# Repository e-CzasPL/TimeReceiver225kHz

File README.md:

# TimeReceiver225kHz
<html>
<body>
<H1>A simple receiver module for decoding a time frame from a 225kHz transmitter PCSK-225 in Solec Kujawski, Poland</h1>

<H2>Content</H2>
<h3>English</h3>
<ul>
  <li><a href="#en1">Changes</li>
  <li><a href="#en1">What's e-Czas</a></li>
  <li><a href="#en2">What's e-Czas Radio?</a></li>
  <li><a href="#en1">Flash programming guide</a></li>
</ul>
<h3>Polski</h3>
<ul>
<li><a href="#pl0">Zmiany</a></li>
<li><a href="#pl1">Co to jest e-Czas?</a></li>
<li><a href="#pl2">Co to jest e-Czas Radio?</a></li>  
<li><a href="#pl3">Instrukcja programowania procesora</a></li>
</ul>
<h2 id="en0">Changes</h2>
<ul>
  <li><b>2024-06-11:</b> Thanks to Damian Jabłoński, who found an error in the scheme. This caused the processor to operate unstablely. Resistor R2 20k (shown in the current schematic) should be added to fix the error.</li>
   <li><b>2024-06-12:</b> 
   The repository contains corrected versions of the project files in KiCAD. In the KiCAD/1.0/bom folder, you can find the interactive BOM in HTML. In the KiCAD/1.0/production folder, you can find production (Gerber) files for fixed PCB.
   </li>
      <li><b>2024-06-14:</b> The repository contains corrected versions firmware. It doesn't need the resistor R2 (20k). Currently is used internal pull-up resistor.
   </li>

</ul>

<h2 id="en1">What's e-Czas</h2>

<p>Providing the service of reliable and reliable distribution of official time signals valid in the territory of the Republic of Poland and signals of the Polish implementation of the international coordinated universal time UTC (PL), based on the state standard for time measurement units and frequency, with the status (guarantee) of official time and synchronization monitoring service.

<h2 id="en2">What's e-Czas Radio?</h2>

<p>The e-Czas Radio service is used to distribute coded official time signals in the territory of the Republic of Poland using long radio waves. End-user synchronization accuracy: &lt;0.01 s

<p>As part of the e-CzasPL project, a service was launched for emitting coded digital time signals on long waves, using the 225 kHz carrier wave of the First Polish Radio Program, from a transmitter located in Poland (a technique similar to the DCF77 (Germany), WWVB (USA), JJY (Japan) system, but based on signal phase modulation), which creates a generally available option to synchronize any time-measuring device with the official time in the Republic of Poland using cheap, energy-saving and simple receiving devices. This technique allows many time-measuring devices to be synchronized to the official time in the Republic of Poland with an accuracy of several or a dozen milliseconds. The system is an additional (redundant) source of time information for users located in Poland.
<p>The standard signals are generated using a stable frequency module based on highly stable rubidium frequency standards in the Radio Broadcasting Center (RCN) in Solec Kujawski. Using receiving devices located at the headquarters of the Central Office of Measures in Warsaw, employees of the Time and Frequency Laboratory remotely monitor changes in the frequency of the carrier wave, as well as monitor the accuracy of encoded time signals and compare them with the Official Time Scale in force in the Republic of Poland generated and maintained in the Central Office of Measures.

<p>The technique using digitally coded time signals involves emitted radio waves from RCN Solec Kujawski and the use of dedicated receivers by end users. You can download documentation related to the technical parameters of the transmitted time signal and a description of the process of making a simplified receiver of coded official time signals on the 225 kHz carrier wave of the First Polish Radio Program.
<br><br>
<ul>
<li>In the "/doc" folder, you will find documentation (in Polish) describing how to encode and receive a time frame. 
<li>In the "/Eagle" folder, you can find the design of the receiver in Autodesk Eagle format. 
<li>In the "/KiCAD" folder, you can find the design of the receiver in KiCAD format. 
<li>In the "/Firmware" folder, you can find firmware for the DSPIC33FJ128GP804 processor in HEX format. 

</ul>

<h3>Power</h3>
<p>The best solution is to use a 5V power supply, e.g. USB. Current consumption is approximately 100mA @ 5V.</p>

<h2 id="en3">Flash programming guide</h2>
<p>I use <a href="https://www.microchip.com/en-us/development-tool/PG164150" target=_blank>PICKIT5, which is not much more expensive than the previous ones and can program without a computer, in the "field." The instructions below describe installing the required software in a Windows 11 environment.
<ol>p
<li>Install <a href="https://www.microchip.com/en-us/tools-resources/develop/mplab-x-ide" target=_blank>MPLAB X IDE</a>
<li>When you install MPLAB and connect PICKIT5 to USB, sometimes the system doesn't recognize it properly. Then open "Device Manager" and check the "Ports (COM & LPT) section. It should look like this:<br><br>
In the "Universal Serial Bus devices"<br><br>If no drivers are installed, this will show<br>>
<br>In the "Microchip Tools"<br>
<br>If the last section does not exist, you must update the drivers on your device, which will appear in the "Universal Serial Bus devices" section.
<li>Without the correct driver, the system will show the error "Failed to get Device ID. Please ensure the target device is attached and try the operation again."
<li>Check the 3V3 power supply at the output of the LM1117 stabilizer
<li>Connect the PICKIT5 programmer to the connector on the board. (pins 1 to 5)
<li>Run MPLAB IPE - specify the path to the HEX file, processor type<br>
<li>Click "Connect", the board must be powered<br>
<li>Program CPU<br>
<li>Turn off the power, disconnect the programmer
</ol>

<h1>Prosty moduł odbiorczy do dekodowania ramek czasu z nadajnika PCSK-225 225kHz w Solcu Kujawskim</h1>

<h2 id="pl0">Zmiany</h2>
<ul>
  <li><b>2024-06-11:</b> Dziękuję Damianowi Jabłońskiemu, który znalazł błąd w schemacie i opracował poprawkę. Błąd skutkował niestabilną pracą procesora. Rozwiązaniem jest dolutowanie rezystora R2 między pinem 3 złącza SV2 a VDD rezystora 20k (R2). Poprawka naniesiona jest na aktualną wersję projektu w KiCAD</li>
   <li><b>2024-06-12:</b> Repozytorium zawiera poprawione pliki projektu. W folderze KiCAD/1.0/bom znajdziesz interaktywny BOM w HTML ułatwiający montaż, w foderze KiCAD/1.0/production są aktualne pliki produkcyjne (Gerber) poprawionego PCB - można je np. wysłać do produkcji (bez rozpakowania).
   </li>
      <li><b>2024-06-14:</b> Repozytorium zawiera poprawiony plik HEX z firmware.  Nie jest konieczne umieszczanie rezystora R2(20k). Obecnie używany jest wewnętrzny rezystor pull-up.
   </li>

</ul>

<h2 id="pl1">Co to jest e-Czas</h2>
Jest tu usługa dystrybucji wiarygodnej i niezawodnej sygnałów czasu urzędowego, obowiązującego na obszarze Rzeczypospolitej Polskiej i sygnałów polskiej realizacji międzynarodowego uniwersalnego czasu koordynowanego UTC(PL), generowanych w oparciu o państwowy wzorzec jednostek miar czasu i częstotliwości, posiadającego status (gwarancję) czasu urzędowego oraz usługi monitorowania synchronizacji.

<h2 id="pl2">Co to jest e-Czas Radio</h2>

<p>Główny Urząd Miar (GUM) uruchomił serwis emitowania kodowanych cyfrowych sygnałów czasu na falach długich, przy wykorzystaniu fali nośnej 225 kHz Programu Pierwszego Polskiego Radia, z nadajnika znajdującego się na terytorium Polski. Jest to technika podobna do systemu DCF77, ale oparta na modulacji fazy sygnału. 
W efekcie powstała ogólnodostępna możliwość zsynchronizowania z czasem urzędowym dowolnego urządzenia odmierzającego czas na obszarze Polski i dużej części Europy przy wykorzystaniu tanich, energooszczędnych i nieskomplikowanych urządzeń odbiorczych. Wykorzystanie tej techniki pozwala na zsynchronizowanie do czasu urzędowego na obszarze RP wielu urządzeń odmierzających czas z dokładnością kilku lub kilkunastu milisekund. System będzie dodatkowym (redundantnym) źródłem informacji o czasie dla użytkowników znajdujących się na terytorium Polski.

<p>Usługa Radia e-Czas służy do dystrybucji kodowanych oficjalnych sygnałów czasu na terytorium Rzeczypospolitej Polskiej za pomocą fal długich radiowych. Dokładność synchronizacji z użytkownikiem końcowym: <0,01 s

<p>W ramach projektu e-CzasPL uruchomiono usługę emisji kodowanych cyfrowych sygnałów czasu na falach długich, wykorzystując falę nośną 225 kHz Pierwszego Programu Polskiego Radia, z nadajnika znajdującego się w Polsce (technika zbliżona do systemu DCF77 (Niemcy), WWVB (USA), JJY (Japonia), ale oparta na modulacji fazy sygnału),  co stwarza ogólnodostępną możliwość synchronizacji dowolnego urządzenia mierzącego czas z czasem urzędowym w Rzeczypospolitej Polskiej za pomocą tanich, energooszczędnych i prostych urządzeń odbiorczych. Technika ta pozwala na synchronizację wielu urządzeń do pomiaru czasu z czasem urzędowym w Rzeczypospolitej Polskiej z dokładnością do kilku lub kilkunastu milisekund. System jest dodatkowym (redundantnym) źródłem informacji o czasie dla użytkowników znajdujących się na terenie Polski.
<p>Sygnały standardowe generowane są w oparciu o moduł częstotliwości stabilnej oparty na wysoce stabilnych wzorcach częstotliwości rubidowych w Radiostacji Nadawczej (RCN) w Solcu Kujawskim. Pracownicy Laboratorium Czasu i Częstotliwości zdalnie monitorują zmiany częstotliwości częstotliwości fali nośnej, a także monitorują dokładność kodowanych sygnałów czasowych i porównują je z obowiązującą w Rzeczypospolitej Polskiej Oficjalną Skalą Czasu generowaną i utrzymywaną w Głównym Urzędzie Miar.

<p>Technika wykorzystująca cyfrowo kodowane sygnały czasu polega na emisji fal radiowych z RCN Solec Kujawski oraz wykorzystaniu dedykowanych odbiorników przez użytkowników końcowych. Można pobrać dokumentację związaną z parametrami technicznymi nadawanego sygnału czasu oraz opis procesu wykonania uproszczonego odbiornika kodowanych oficjalnych sygnałów czasu na fali nośnej 225kHz Pierwszego Programu Polskiego Radia (PCSK-225).
<br><br>
<ul>
<li>W folderze "/doc" znajdziesz dokumentację opisującą sposób kodowania i odbierania ram czasowych. 
<li>W folderze "/Eagle" znajduje się projekt odbiornika w formacie Autodesk Eagle. 
<li>W folderze "/KiCAD" znajduje się projekt odbiornika w formacie KiCAD. 
<li>W folderze "/Firmware" można znaleźć oprogramowanie układowe dla DSPIC33FJ128GP804 procesora w formacie HEX. 

</ul>
<h3>Zasilanie</h3>
<p>Najlepszym rozwiązaniem jest użycie zasilania 5V np. USB. Pobór prądu wynosi ok 100mA przy 5V.</p>

<h2 id="pl3">Instrukcja programowania procesora</h2>
<p>Ja używam <a href="https://www.microchip.com/en-us/development-tool/PG164150" target=_blank>PICKIT5, niewiele droższy od poprzednich a mający dodatkowo możliwość programowania bez komputera, w "polu". Poniżej opisuje instalację wymaganego oprogramowania w środowisku Windows 11.
<ol>
<li>Zainstaluj <a href="https://www.microchip.com/en-us/tools-resources/develop/mplab-x-ide" target=_blank>MPLAB X IDE</a>
<li>Po zainstalowaniu MPLAB i podłaczeniu PICKIT5 do USB czasami system nie rozpoznaje go prawidłowo. Wtedy otwórz "Device Manager" i sprawdź sekcję "Ports (COM & LPT). Powinna wyglądać tak:<br><br>
W sekcji "Universal Serial Bus devices"<br><br>Jeżeli nie są zainstalowane sterowniki, pokaże się to<br>>
<br>W sekcji "Microchip Tools"<br>
<br>Jeżeli ostatnia sekcja nie istnieje należy zaktualizować sterowniki w urządzeniu które pojawi się w sekcji "Universal Serial Bus devices".
<li>Bez prawidłowego sterownika, system pokaże błąd "Failed to get Device ID. Please make sure the target device is attached and try the operation again."
<li> sprawdzić zasilanie 3V3 na wyjściu stabilizatora LM1117
<li>Podłączyć programator PICKIT5 do złącza na płytce. (piny od 1 do 5)
<li>Uruchomić program MPLAB IPE - podać ścieżgę do pliku HEX, typ procesora<br>
<li>Kliknąć "Connect", płytka musi być zasilana<br>
<li>Zaprogramować procesor<br>
<li>Wyłączyć zasilanie, odłączyć programator
</ol>

<h2>Projekty połączone</h2>
<ol>
<li><a href="https://github.com/J-K-Kowalski/PCSK225-Antenna" target="_blank">Antena aktywna na tranzystorze FET</a></li>
<li><a href="https://github.com/J-K-Kowalski/PCSK225_RECV_USB" target="_blank">Odbiornik z interfejsem USB</a></li>
<li><a href="https://github.com/sp5wwp/e-Czas" target="_blank">SP5WWP - Dekoder e-Czas</a></li>
<li><a href="https://github.com/sp6hfe/e-CzasPL" target="_blank">e-CzasPL Radio reference C++ data decoder by SP6HFE</a></li>
</ol>

<p>Jurek K. Kowalski
<p>
<table border=0 cellpadding=0 cellspacing=0 width="100%"><tr>
<td align=left>

</td>
<td align=right>
</td>
</tr>
</table>
</body>
</html>

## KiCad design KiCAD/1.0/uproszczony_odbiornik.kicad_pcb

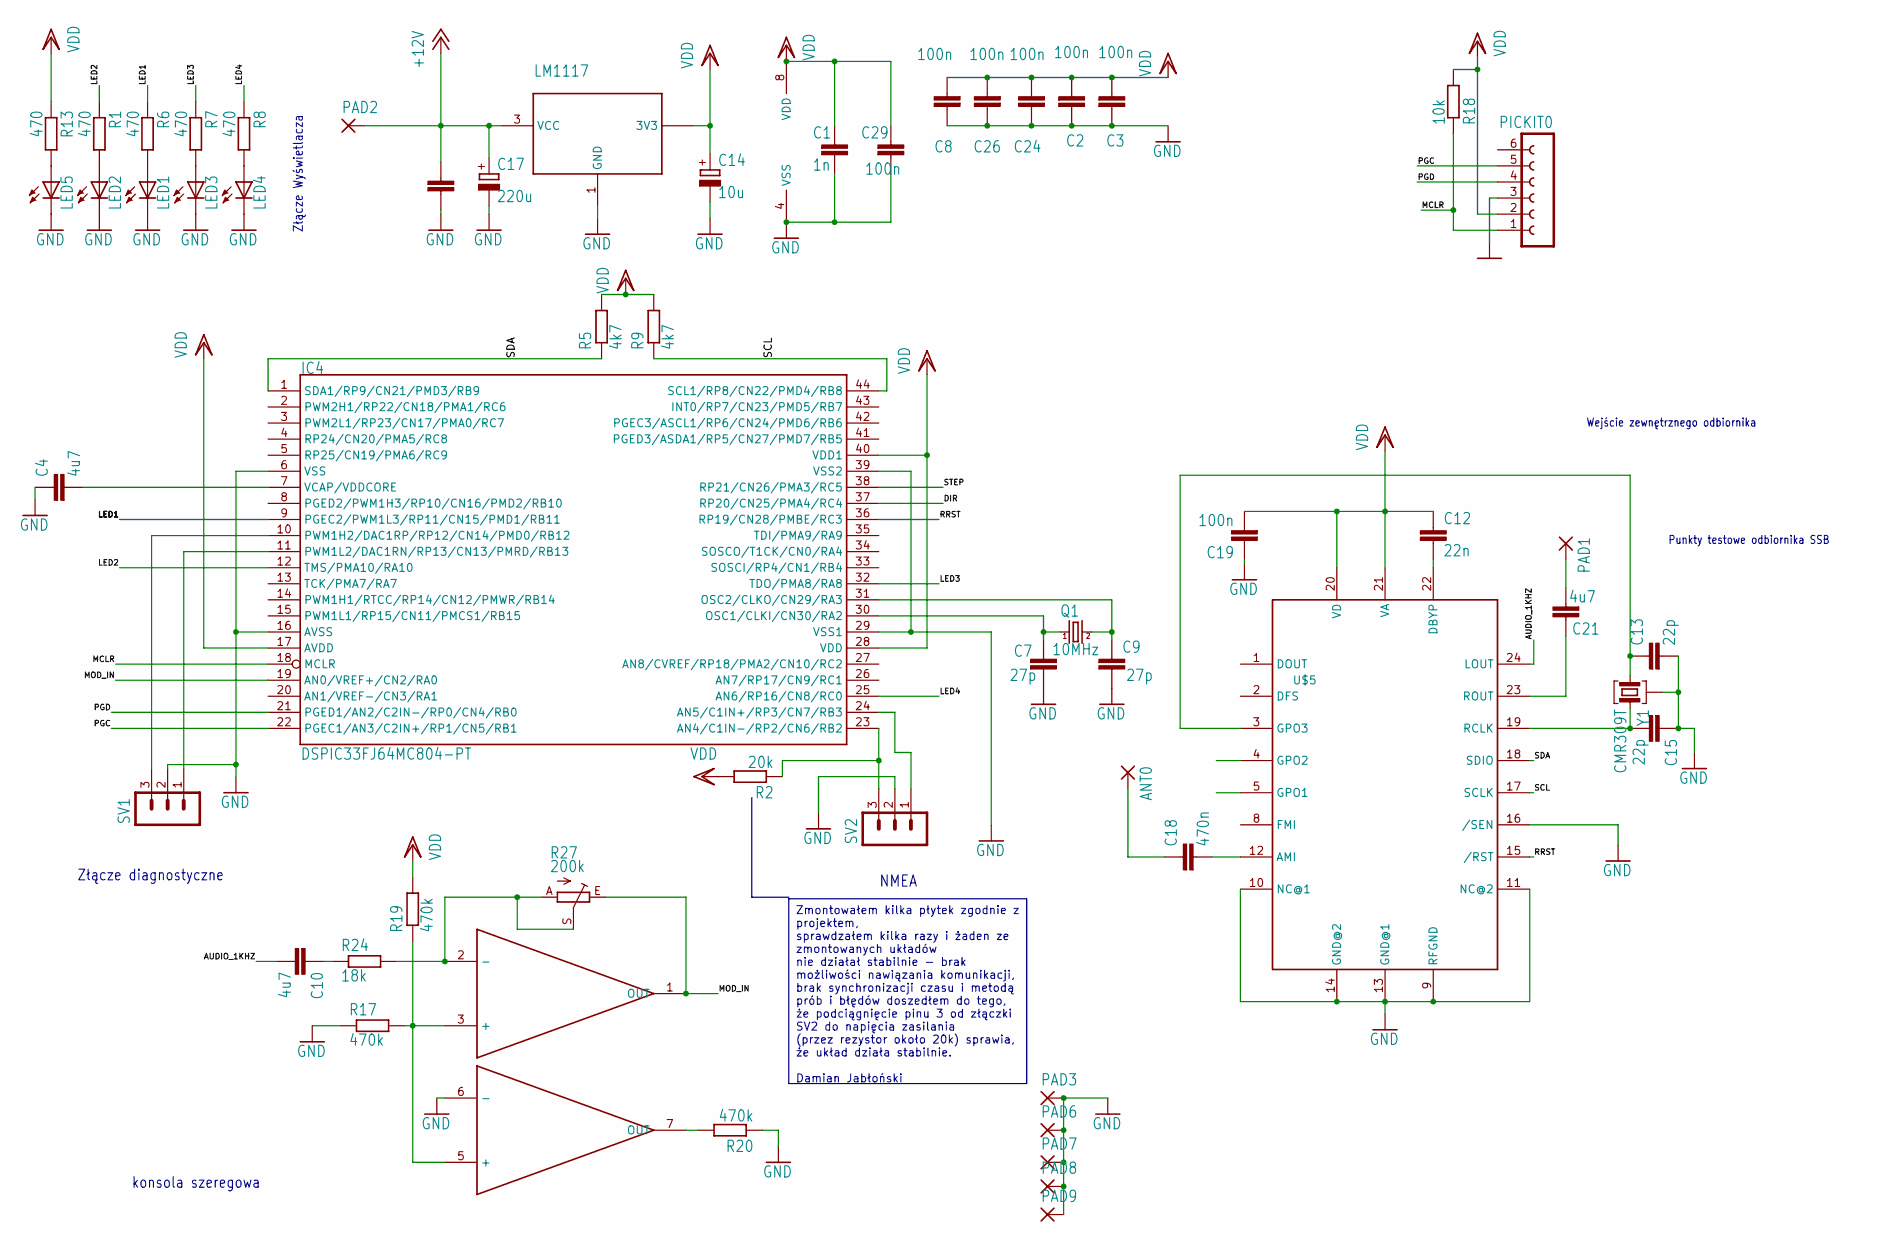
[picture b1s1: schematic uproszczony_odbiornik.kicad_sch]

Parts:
ANT0: 1,6/0,9; 1,6_0,9
C1: 1n; C0805K
C2, C3, C5, C8, C24, C26, C29: 100n; C0805K
C4: 4u7; C0805K
C7, C9: 27p; C0805K
C10, C21: 4u7; C0603K
C12: 22n; C0603K
C13, C15: 22p; C0603K
C14: 10u; SMC_B
C17: 220u; SMC_B
C18: 470n; C0603K
C19: 100n; C0603K
IC4: DSPIC33FJ64MC804-PT; TQFP44
LED1, LED2, LED3, LED4, LED5: LEDCHIP-LED0805; CHIP-LED0805
PAD1, PAD2, PAD3, PAD6, PAD7, PAD8, PAD9: 1,6/0,9; 1,6_0,9
PICKIT0: FE06-1; FE06
Q1: 10MHz; HC49U-V
R1, R6, R7, R8, R13: 470; R0805
R2: 20k; R0805
R5, R9: 4k7; R0805
R17, R19, R20: 470k; M0805
R18: 10k; R0805
R24: 18k; M0805
R27: 200k; RJ9W
SV1, SV2: MA03-1
U$1: MCP607SO8; SOIC8
U$3: LM1117; SOT223-3
U$5: SI4735-D60; SSOP24
Y1: CMR309T

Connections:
+12V: C5.1, C17.+, PAD2.1, U$3.3 (VCC)
/AUDIO_1KHZ: C10.2, U$5.24 (LOUT)
/DIR: IC4.37 (RP20/CN25/PMA4/RC4)
/LED1: IC4.9 (PGEC2/PWM1L3/RP11/CN15/PMD1/RB11), R6.1
/LED2: IC4.12 (TMS/PMA10/RA10), R1.1
/LED3: IC4.32 (TDO/PMA8/RA8), R7.1
/LED4: IC4.25 (AN6/RP16/CN8/RC0), R8.1
/MCLR: IC4.18 (MCLR), PICKIT0.1, R18.1
/MOD_IN: IC4.19 (AN0/VREF+/CN2/RA0), R27.E, U$1.1 (OUT)
/PGC: IC4.22 (PGEC1/AN3/C2IN+/RP1/CN5/RB1), PICKIT0.5
/PGD: IC4.21 (PGED1/AN2/C2IN-/RP0/CN4/RB0), PICKIT0.4
/RRST: IC4.36 (RP19/CN28/PMBE/RC3), U$5.15 (/RST)
/SCL: IC4.44 (SCL1/RP8/CN22/PMD4/RB8), R9.1, U$5.17 (SCLK)
/SDA: IC4.1 (SDA1/RP9/CN21/PMD3/RB9), R5.1, U$5.18 (SDIO)
/STEP: IC4.38 (RP21/CN26/PMA3/RC5)
GND: C1.2, C2.2, C3.2, C4.1, C5.2, C7.2, C8.1, C9.2, C13.2, C14.-, C15.1, C17.-, C19.1, C24.1, C26.1, C29.2, IC4.6 (VSS), IC4.16 (AVSS), IC4.29 (VSS1), IC4.39 (VSS2), LED1.C, LED2.C, LED3.C, LED4.C, LED5.C, PAD3.1, PAD6.1, PAD7.1, PAD8.1, PAD9.1, PICKIT0.3, R17.1, R20.1, SV1.2, SV2.2, U$1.4 (VSS), U$1.6 (-), U$3.1 (GND), U$5.9 (RFGND), U$5.10 (NC@1), U$5.11 (NC@2), U$5.13 (GND@1), U$5.14 (GND@2), U$5.16 (/SEN), Y1.3 (G)
unnamed: ANT0.1, C18.1
unnamed: C10.1, R24.1
unnamed: IC4.23 (AN4/C1IN-/RP2/CN6/RB2), R2.1, SV2.3
unnamed: IC4.24 (AN5/C1IN+/RP3/CN7/RB3), SV2.1
unnamed: C7.1, IC4.30 (OSC1/CLKI/CN30/RA2), Q1.1
unnamed: C9.1, IC4.31 (OSC2/CLKO/CN29/RA3), Q1.2
unnamed: IC4.10 (PWM1H2/DAC1RP/RP12/CN14/PMD0/RB12), SV1.3
unnamed: IC4.11 (PWM1L2/DAC1RN/RP13/CN13/PMRD/RB13), SV1.1
unnamed: C4.2, IC4.7 (VCAP/VDDCORE)
unnamed: LED1.A, R6.2
unnamed: LED2.A, R1.2
unnamed: LED3.A, R7.2
unnamed: LED4.A, R8.2
unnamed: LED5.A, R13.2
unnamed: C21.2, PAD1.1
unnamed: R17.2, R19.1, U$1.3 (+), U$1.5 (+)
unnamed: R24.2, R27.A, R27.S, U$1.2 (-)
unnamed: R20.2, U$1.7 (OUT)
unnamed: C18.2, U$5.12 (AMI)
unnamed: C12.2, U$5.22 (DBYP)
unnamed: C13.1, U$5.3 (GPO3), Y1.1
unnamed: C15.2, U$5.19 (RCLK), Y1.2
unnamed: C21.1, U$5.23 (ROUT)
VDD: C1.1, C2.1, C3.1, C8.2, C12.1, C14.+, C19.2, C24.2, C26.2, C29.1, IC4.17 (AVDD), IC4.28 (VDD), IC4.40 (VDD1), PICKIT0.2, R2.2, R5.2, R9.2, R13.1, R18.2, R19.2, U$1.8 (VDD), U$3.2 (3V3), U$3.4 (3V3), U$5.20 (VD), U$5.21 (VA)

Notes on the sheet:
Zmontowałem kilka płytek zgodnie z projektem, sprawdzałem kilka razy i żaden ze zmontowanych układów nie działał stabilnie - brak możliwości nawiązania komunikacji, brak synchronizacji czasu i metodą prób i błędów doszedłem do tego, że podciągnięcie pinu 3 od złączki SV2 do napięcia zasilania (prze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
Złącze diagnostyczne
Wejście zewnętrznego odbiornika
Złącze Wyświetlacza
Punkty testowe odbiornika SSB
konsola szeregowa
NMEA

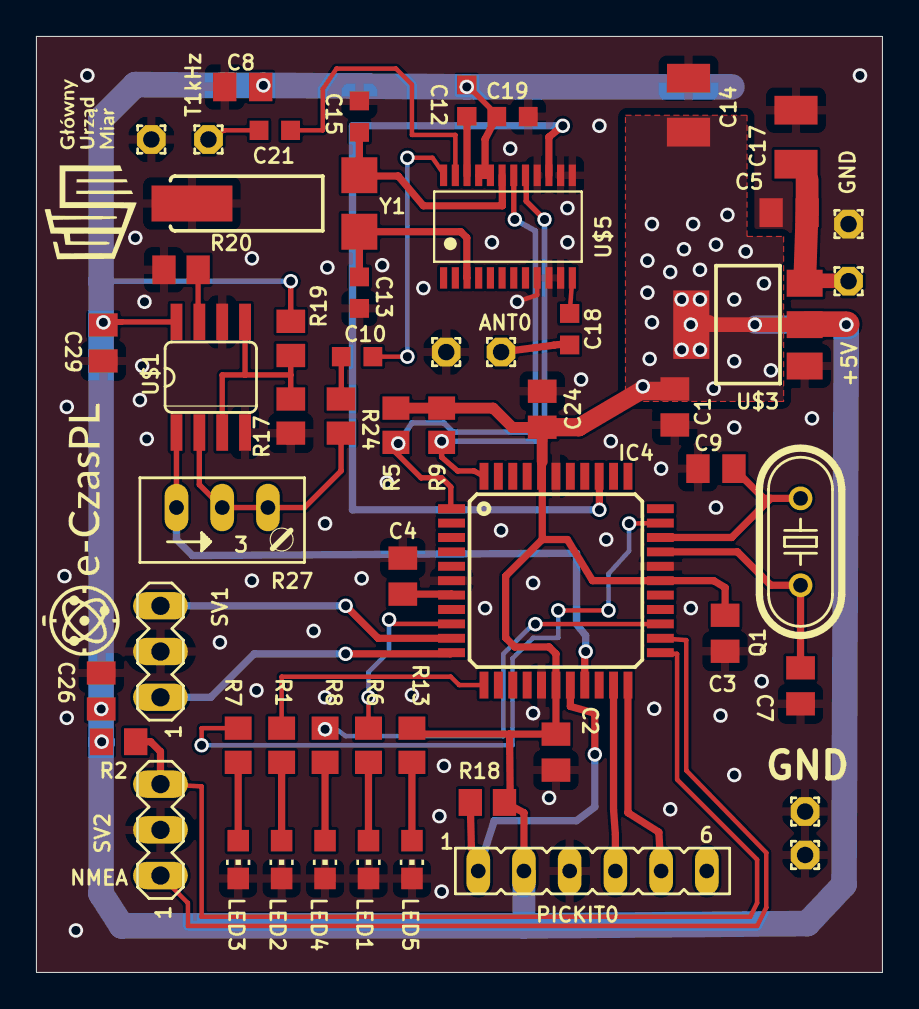
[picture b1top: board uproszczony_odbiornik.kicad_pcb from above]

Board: 2 copper layers, 47.0 x 52.0 mm, 56 parts (0 on the bottom side), 38 nets.

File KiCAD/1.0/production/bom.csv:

Designator,Footprint,Quantity,Value,LCSC Part #
"ANT0, PAD1, PAD2, PAD3, PAD6, PAD7, PAD8, PAD9","1,6_0,9",8,"1,6/0,9",
C1,C0805K,1,1n,
"C10, C21",C0603K,2,4u7,
C12,C0603K,1,22n,
"C13, C15",C0603K,2,22p,
C14,SMC_B,1,10u,
C17,SMC_B,1,220u,
C18,C0603K,1,470n,
C19,C0603K,1,100n,
"C2, C24, C26, C29, C3, C5, C8",C0805K,7,100n,
C4,C0805K,1,4u7,
"C7, C9",C0805K,2,27p,
IC4,TQFP44,1,DSPIC33FJ64MC804-PT,
"LED1, LED2, LED3, LED4, LED5",CHIP-LED0805,5,LEDCHIP-LED0805,
PICKIT0,FE06,1,FE06-1,
Q1,HC49U-V,1,10MHz,
"R1, R13, R6, R7, R8",R0805,5,470,
"R17, R19, R20",M0805,3,470k,
R18,R0805,1,10k,
R2,R0805,1,20k,
R24,M0805,1,18k,
R27,RJ9W,1,200k,
"R5, R9",R0805,2,4k7,
"SV1, SV2",MA03-1,2,MA03-1,
U$1,SOIC8,1,MCP607SO8,
U$3,SOT223-3,1,LM1117,
U$5,SSOP24,1,SI4735-D60,
Y1,CMR309T,1,CMR309T,

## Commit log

2024-03-26 Create doc
2024-03-26 add documentation polish
2024-03-26 add info to readme.md
2024-03-26 add KiCAD project
2024-03-28 add english version of documentation
2024-04-01 modification of Readme, add firmware
2024-04-06 add pcb_components.pdf
2024-04-15 modify readme
2024-06-12 fix schematics and PCB, Add R2
2024-06-12 change read.me
2024-06-12 change image
2024-06-14 new version of firmware, fixed pull-up pin 23 problem
2024-06-15 changes in readme
2024-10-01 poprawione literówki i kolejność projektów
